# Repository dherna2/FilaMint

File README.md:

# FilaMint Team4

## This github was created for ECE411 Practicum Fall 2016  

### Collaborators are:

Colleen Nhim  
Nettaly Rebolledo  
David Hernandez  
Srijana Sapkota  

We used [Google drive] to simultanelously work on documents.  
Our finished documents have been transferred to the [Wiki](../../wiki) or saved in the folder named documents. 

[Google drive]: https://drive.google.com/drive/u/1/folders/0B7ei5UTStXl6bGFZWWxhMDdIQzQ

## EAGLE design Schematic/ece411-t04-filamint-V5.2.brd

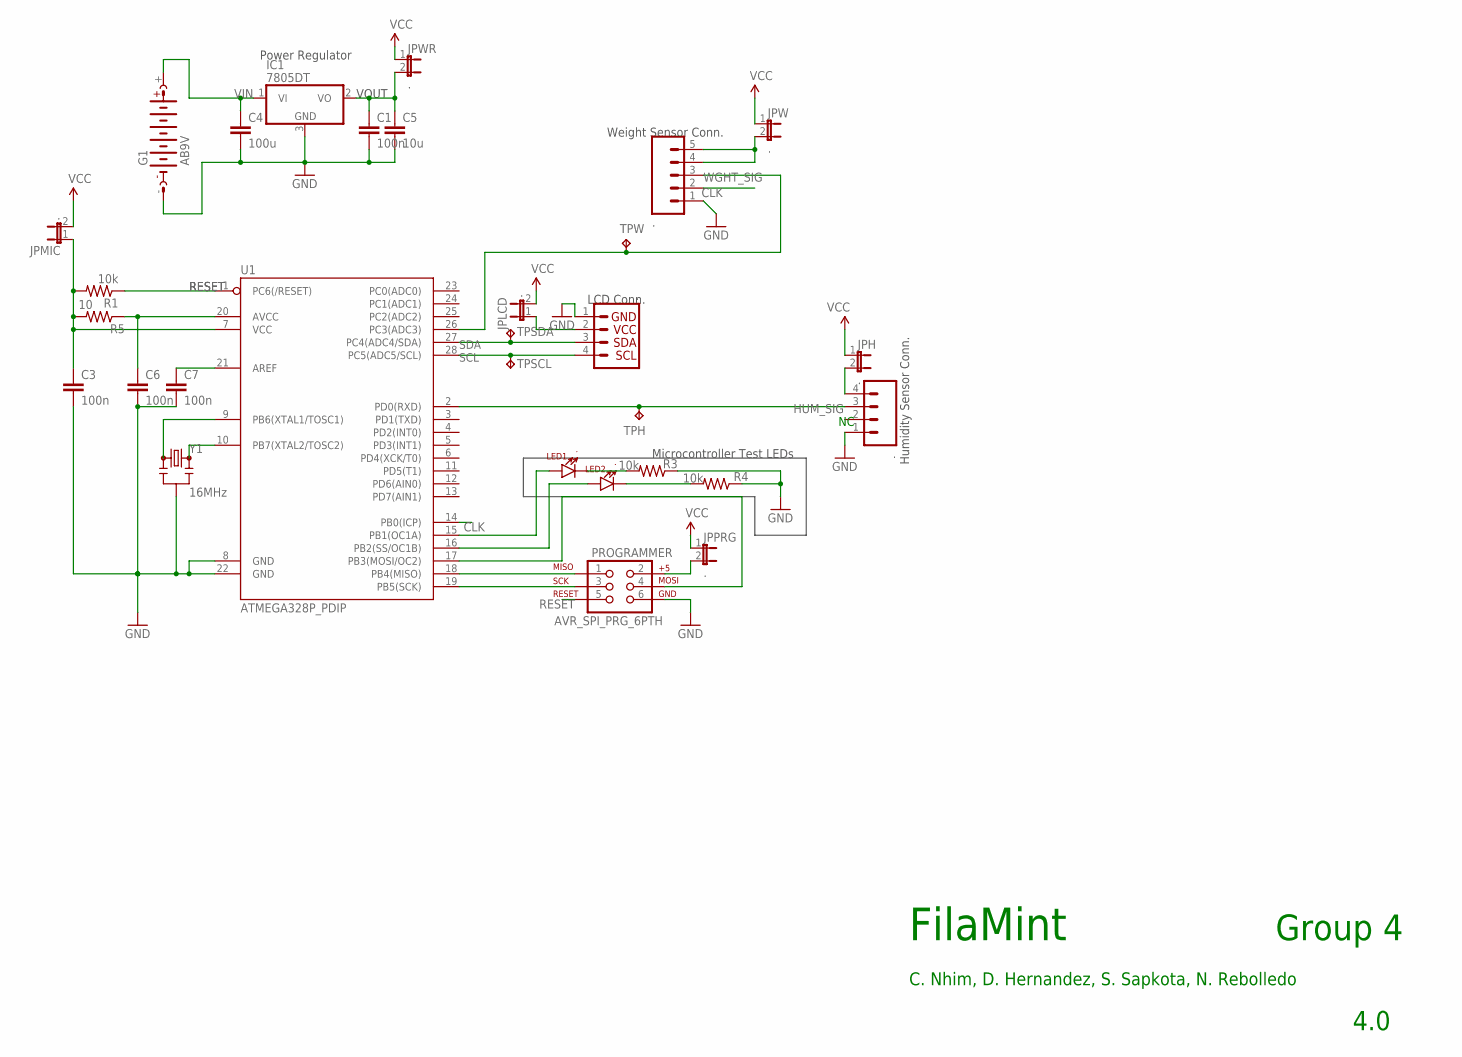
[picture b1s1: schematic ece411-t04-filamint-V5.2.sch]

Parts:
C1, C3, C6, C7: 100n; C0805
C4: 100u; C025-024X044
C5: 10u; C025-024X044
DHT22: .; 1X04-1MM-RA
G1: AB9V
HX711: .; 1X05-1MM
IC1: 7805DT; TO252
JPH: .; JP1
JPLCD: .; JP1
JPMIC: .; JP1
JPPRG: .; JP1
JPW: .; JP1
JPWR: .; JP1
LCD: .; 1X04
LED1, LED2: .; LTE-302
PROGRAMMER: AVR_SPI_PRG_6PTH; 2X3
R1, R3, R4: 10k; 0204/5
R5: 10; 0204/5
TPH: TPB1,27; B1,27
TPSCL: TPB1,27; B1,27
TPSDA: TPB1,27; B1,27
TPW: TPB1,27; B1,27
U1: ATMEGA328P_PDIP; DIL28-3
Y1: 16MHz; RESONATOR-PTH

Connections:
AVCC: C6.1, R5.1, U1.20 (AVCC)
CLK: HX711.2, U1.14 (PB0(ICP))
GND: C1.2, C3.2, C4.2, C5.2, C6.2, C7.2, DHT22.1, G1.-, HX711.1, IC1.3 (GND), LCD.1, PROGRAMMER.6, R3.1, R4.1, U1.8 (GND), U1.22 (GND), Y1.2
HUM_SIG: DHT22.3, TPH.TP, U1.2 (PD0(RXD))
MISO: PROGRAMMER.1, U1.18 (PB4(MISO))
MOSI: PROGRAMMER.4, U1.17 (PB3(MOSI/OC2))
unnamed: U1.9 (PB6(XTAL1/TOSC1)), Y1.1
unnamed: U1.10 (PB7(XTAL2/TOSC2)), Y1.3
unnamed: HX711.4, HX711.5, JPW.2
unnamed: C7.1, U1.21 (AREF)
unnamed: LED1.A, U1.15 (PB1(OC1A))
unnamed: LED2.A, U1.16 (PB2(SS/OC1B))
unnamed: DHT22.4, JPH.2
unnamed: LED1.C, R3.2
unnamed: LED2.C, R4.2
unnamed: JPPRG.2, PROGRAMMER.2
unnamed: C3.1, JPMIC.1, R1.2, R5.2, U1.7 (VCC)
unnamed: JPLCD.1, LCD.2
unnamed: C1.1, C5.1, IC1.2 (VO), JPWR.2
RESET: PROGRAMMER.5, R1.1, U1.1 (PC6(/RESET))
SCK: PROGRAMMER.3, U1.19 (PB5(SCK))
SCL: LCD.4, TPSCL.TP, U1.28 (PC5(ADC5/SCL))
SDA: LCD.3, TPSDA.TP, U1.27 (PC4(ADC4/SDA))
VCC: JPH.1, JPLCD.2, JPMIC.2, JPPRG.1, JPW.1, JPWR.1
VIN: C4.1, G1.+, IC1.1 (VI)
WGHT_SIG: HX711.3, TPW.TP, U1.26 (PC3(ADC3))

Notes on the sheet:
Weight Sensor Conn.
Humidity Sensor Conn.
LCD Conn.
Power Regulator
FilaMint
4.0
C. Nhim, D. Hernandez, S. Sapkota, N. Rebolledo
Group 4
VOUT
Microcontroller Test LEDs

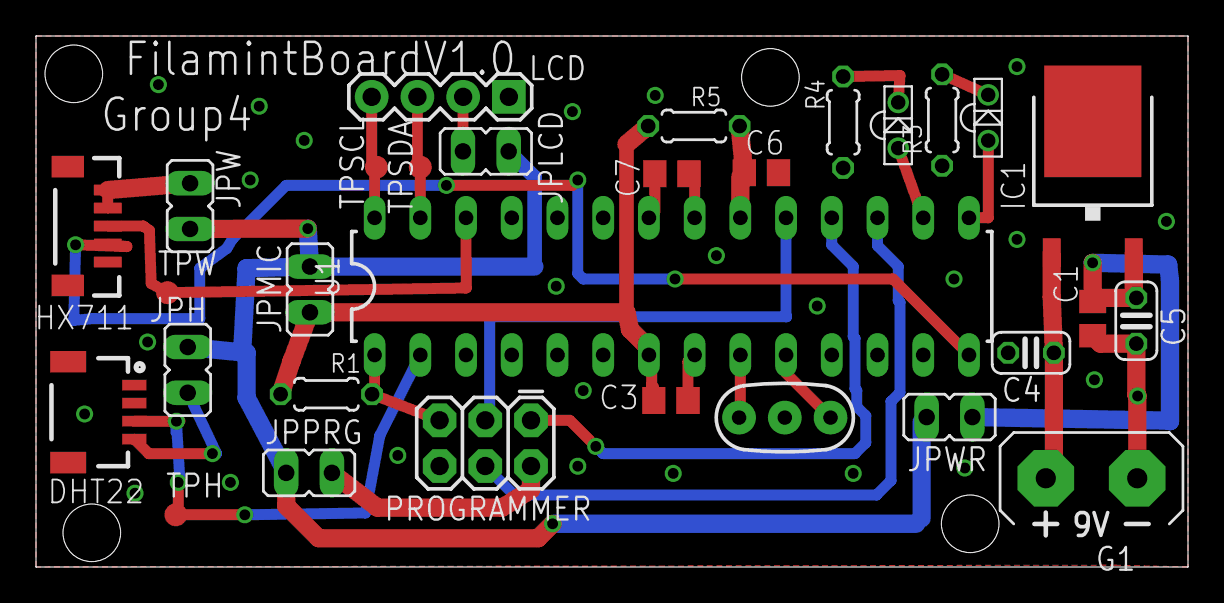
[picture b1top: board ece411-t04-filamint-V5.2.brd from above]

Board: 2 copper layers, 64.0 x 29.5 mm, 30 parts (0 on the bottom side), 26 nets.

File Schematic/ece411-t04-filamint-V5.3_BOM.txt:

Partlist exported from C:/Users/David_desk/Documents/eagle/ece411-t04-filamint-V5.3.sch at 11/28/2016 12:37 PM

Qty Value            Device           Package       Parts                               Description                                                               TP_SIGNAL_NAME
1   .                I2C_STANDARD     1X04          LCD                                 SparkFun has standardized on a pinout for all I2C based sensor breakouts.               
6   .                JP1E             JP1           JPH, JPLCD, JPMIC, JPPRG, JPW, JPWR JUMPER                                                                                  
2   .                LTE-302          LTE-302       LED1, LED2                          Through-hole side-firing 940nm IR LED                                                   
1   .                M04SMD2          1X04-1MM-RA   DHT22                               Header 4                                                                                
1   .                M05SMD           1X05-1MM      HX711                               Header 5                                                                                
1   10               R-US_0204/5      0204/5        R5                                  RESISTOR, American symbol                                                               
4   100n             C-EUC0805        C0805         C1, C3, C6, C7                      CAPACITOR, European symbol                                                              
1   100u             C-EU025-024X044  C025-024X044  C4                                  CAPACITOR, European symbol                                                              
3   10k              R-US_0204/5      0204/5        R1, R3, R4                          RESISTOR, American symbol                                                               
1   10u              C-EU025-024X044  C025-024X044  C5                                  CAPACITOR, European symbol                                                              
1   16MHz            RESONATORPTH     RESONATOR-PTH Y1                                  Resonator                                                                               
1   7805DT           7805DT           TO252         IC1                                 Positive VOLTAGE REGULATOR                                                              
1   AB9V             AB9V             AB9V          G1                                  9-V BATTERY CLIP                                                                        
1   ATMEGA328P_PDIP  ATMEGA328P_PDIP  DIL28-3       U1                                  uC used in the Arduino                                                                  
1   AVR_SPI_PRG_6PTH AVR_SPI_PRG_6PTH 2X3           PROGRAMMER                          AVR ISP 6 Pin                                                                           
4   TPB1,27          TPB1,27          B1,27         TPH, TPSCL, TPSDA, TPW              Test pad

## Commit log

2016-10-11 added chat history
2016-10-26 Submitted HW3 10/25
2016-10-26 Update/Create 2016-10-26-HW-3--Requirements.md
2016-10-26 HW3 html
2016-10-26 HW3 Final Rev
    submitted 10/25/2016
2016-10-26 Create HW3 Submitted
2016-10-26 Rename HW3 Submitted to HW3 Submitted.md
2016-10-26 Submitted on 10/25/2016
2016-10-27 SparkFun library
    Install library and search for *atmega328* select PDIP not EZ
2016-10-30 LCD shield info
    PDF with assembly and example code reference
2016-10-30 FilaMint LCD Arduino Code
    This is the code for the LCD display
2016-10-30 test
2016-10-30 Arduino LCD Code REV 2
2016-10-30 Schematic
    V3
2016-11-03 Add files via upload
    I dont know what the leds do
2016-11-03 Rename Filamint Schematic V4.1.txt to Filamint Schematic V4.1_BOM.txt
2016-11-03 Rev4
    I added some testpoints, jumpers, values to connectors (so ERC pass) and moved the connectors to one side. It passes ERC with 2 approves!
2016-11-03 ERC screen cap V4.3
2016-11-03 Add files via upload
    grouped the LEDs
2016-11-05 organization
    added folders
2016-11-07 changed wiki to readme
2016-11-07 Rename Filamint Schematic V4.1.txt to Filamint Schematic V4.1 BOM.txt
2016-11-10 v4.5
    changed batt, microprosser footprint
2016-11-10 very*very* rough draft
2016-11-10 draft2-v.4.6
    fixed gnd plane and missing reset connection
2016-11-13 notes
2016-11-13 readme
2016-11-13 Add files via upload
    This is the library so we can use LCD shield
2016-11-13 use this instead of helloworld
2016-11-14 lcd and humidity
2016-11-14 all sensors
2016-11-14 Rename code/LCD/RGBLCD_Library/examples/HelloWorld/HelloWorld.ino/HelloWorld.ino.ino to code/LCD/RGBLCD_Library/examples/HelloWorld.ino
2016-11-14 Rename code/LCD/RGBLCD_Library/examples/HelloWorld.ino to code/LCD/RGBLCD_Library/HelloWorld2.ino
2016-11-14 Rename FilaMint_rev_3.ino to code/FilaMint_rev_3.ino
2016-11-14 Rename hx711 board connection.txt to code/weight/hx711 board connection.txt
2016-11-14 Rename code/FilaMint_LCD.ino to code/LCD/RGBLCD_Library/HelloWorld/FilaMint_LCD_rev0.ino
2016-11-14 Rename filamint_lcd.ino to filamint_lcd_Rev1.ino
2016-11-14 Rename code/FilaMint_rev_3.ino to code/LCD/RGBLCD_Library/HelloWorld/FilaMint_rev_3.ino
2016-11-14 humidity only
2016-11-16 made changes that andrew suggested
    thicker powerlines, rearrange closer
2016-11-16 after meeting with andrew
    final version
2016-11-17 minor changes
    widen some vcc lines, bigger mounting holes 3.2mm
2016-11-17 added bottom silk
    getting error on OSH park saying no bottom silk
2016-11-17 Submitted to OSH Park
    added one via for more copper filling
2016-11-17 Homework 5
2016-11-20 seperating lines
2016-11-20 line seperation
2016-11-20 added high hum text
    cleaned up by removing hx711 files and creating library
2016-11-20 Rename code/filamint_lcd_wght_hum_Rev3/Readme.md to code/filamint_lcd_wght_hum_RevReadme.md
2016-11-20 Rename code/filamint_lcd_wght_hum_RevReadme.md to code/filamint_lcd_wght_hum/Readme.md
2016-11-20 Rename code/filamint_lcd_wght_hum_Rev3/HX711.cpp to code/weight/filamint_wght_rev3/HX711.cpp
2016-11-20 Rename code/filamint_lcd_wght_hum_Rev3/HX711.h to code/weight/filamint_wght_rev3/HX711.h
2016-11-20 Rename code/filamint_lcd_wght_hum_Rev3/filamint_lcd_wght_hum_Rev3.ino to code/filamint_lcd_wght_hum/filamint_lcd_wght_hum_Rev3.ino
2016-11-20 notes on rev3 and rev4
2016-11-28 BOM sorted by value
2016-12-03 hx711
2016-12-03 Add files via upload
    Added functions for the buttons:
    Left: ABS filament selection
    Right: PLS button selection
    Up: Humidity and weight display
    Select: Main screen
2016-12-03 Add files via upload
    Adding button functions
    Select: Main screen
    Up: Humidity and weigh readings
    Left: ABS type filament selection
    Right: PLA type filament selection
2016-12-04 328p
2016-12-04 updated pins
2016-12-04 pis updated
2016-12-04 pin update
2016-12-04 added references to filamint board
2016-12-04 pin assignment update
2016-12-04 pin assignment
2016-12-04 rename folder
2016-12-04 rename file
2016-12-04 rename
2016-12-04 humidity connections
2016-12-04 Rename readme to readme.md
2016-12-04 lcd zip file
2016-12-04 move readme
2016-12-04 moving file
2016-12-04 load sensor connection pictures
2016-12-04 adjusted pins
2016-12-04 Add files via upload
    Filamint laser cutting lid and bottom.
    Make sure 2 pieces (lid, bottom). The dimensions need to be 10" x 4.5".
2016-12-04 pins adjusted
    shorted pin 2 and 4 for humidity signal
2016-12-05 filamint pictures
2016-12-05 sch picture
2016-12-05 adding pictures
2016-12-05 arduino 328p pinout
2016-12-05 added 328p pinout
2016-12-06 Now errors if humidity no connected
2016-12-06 David's updates
    added version number, welcome screen back and more comments
2016-12-08 Add files via upload
    David, here is the stl file for 3d printing.
    -Colleen
2016-12-08 laser cutting case pt 1
2016-12-08 Create LICENSE
2016-12-08 organization
    moving files around

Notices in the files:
parts and their libraries:
SparkFun-Connectors: Licensing: Creative Commons ShareAlike 4.0 International - https://creativecommons.org/licenses/by-sa/4.0
